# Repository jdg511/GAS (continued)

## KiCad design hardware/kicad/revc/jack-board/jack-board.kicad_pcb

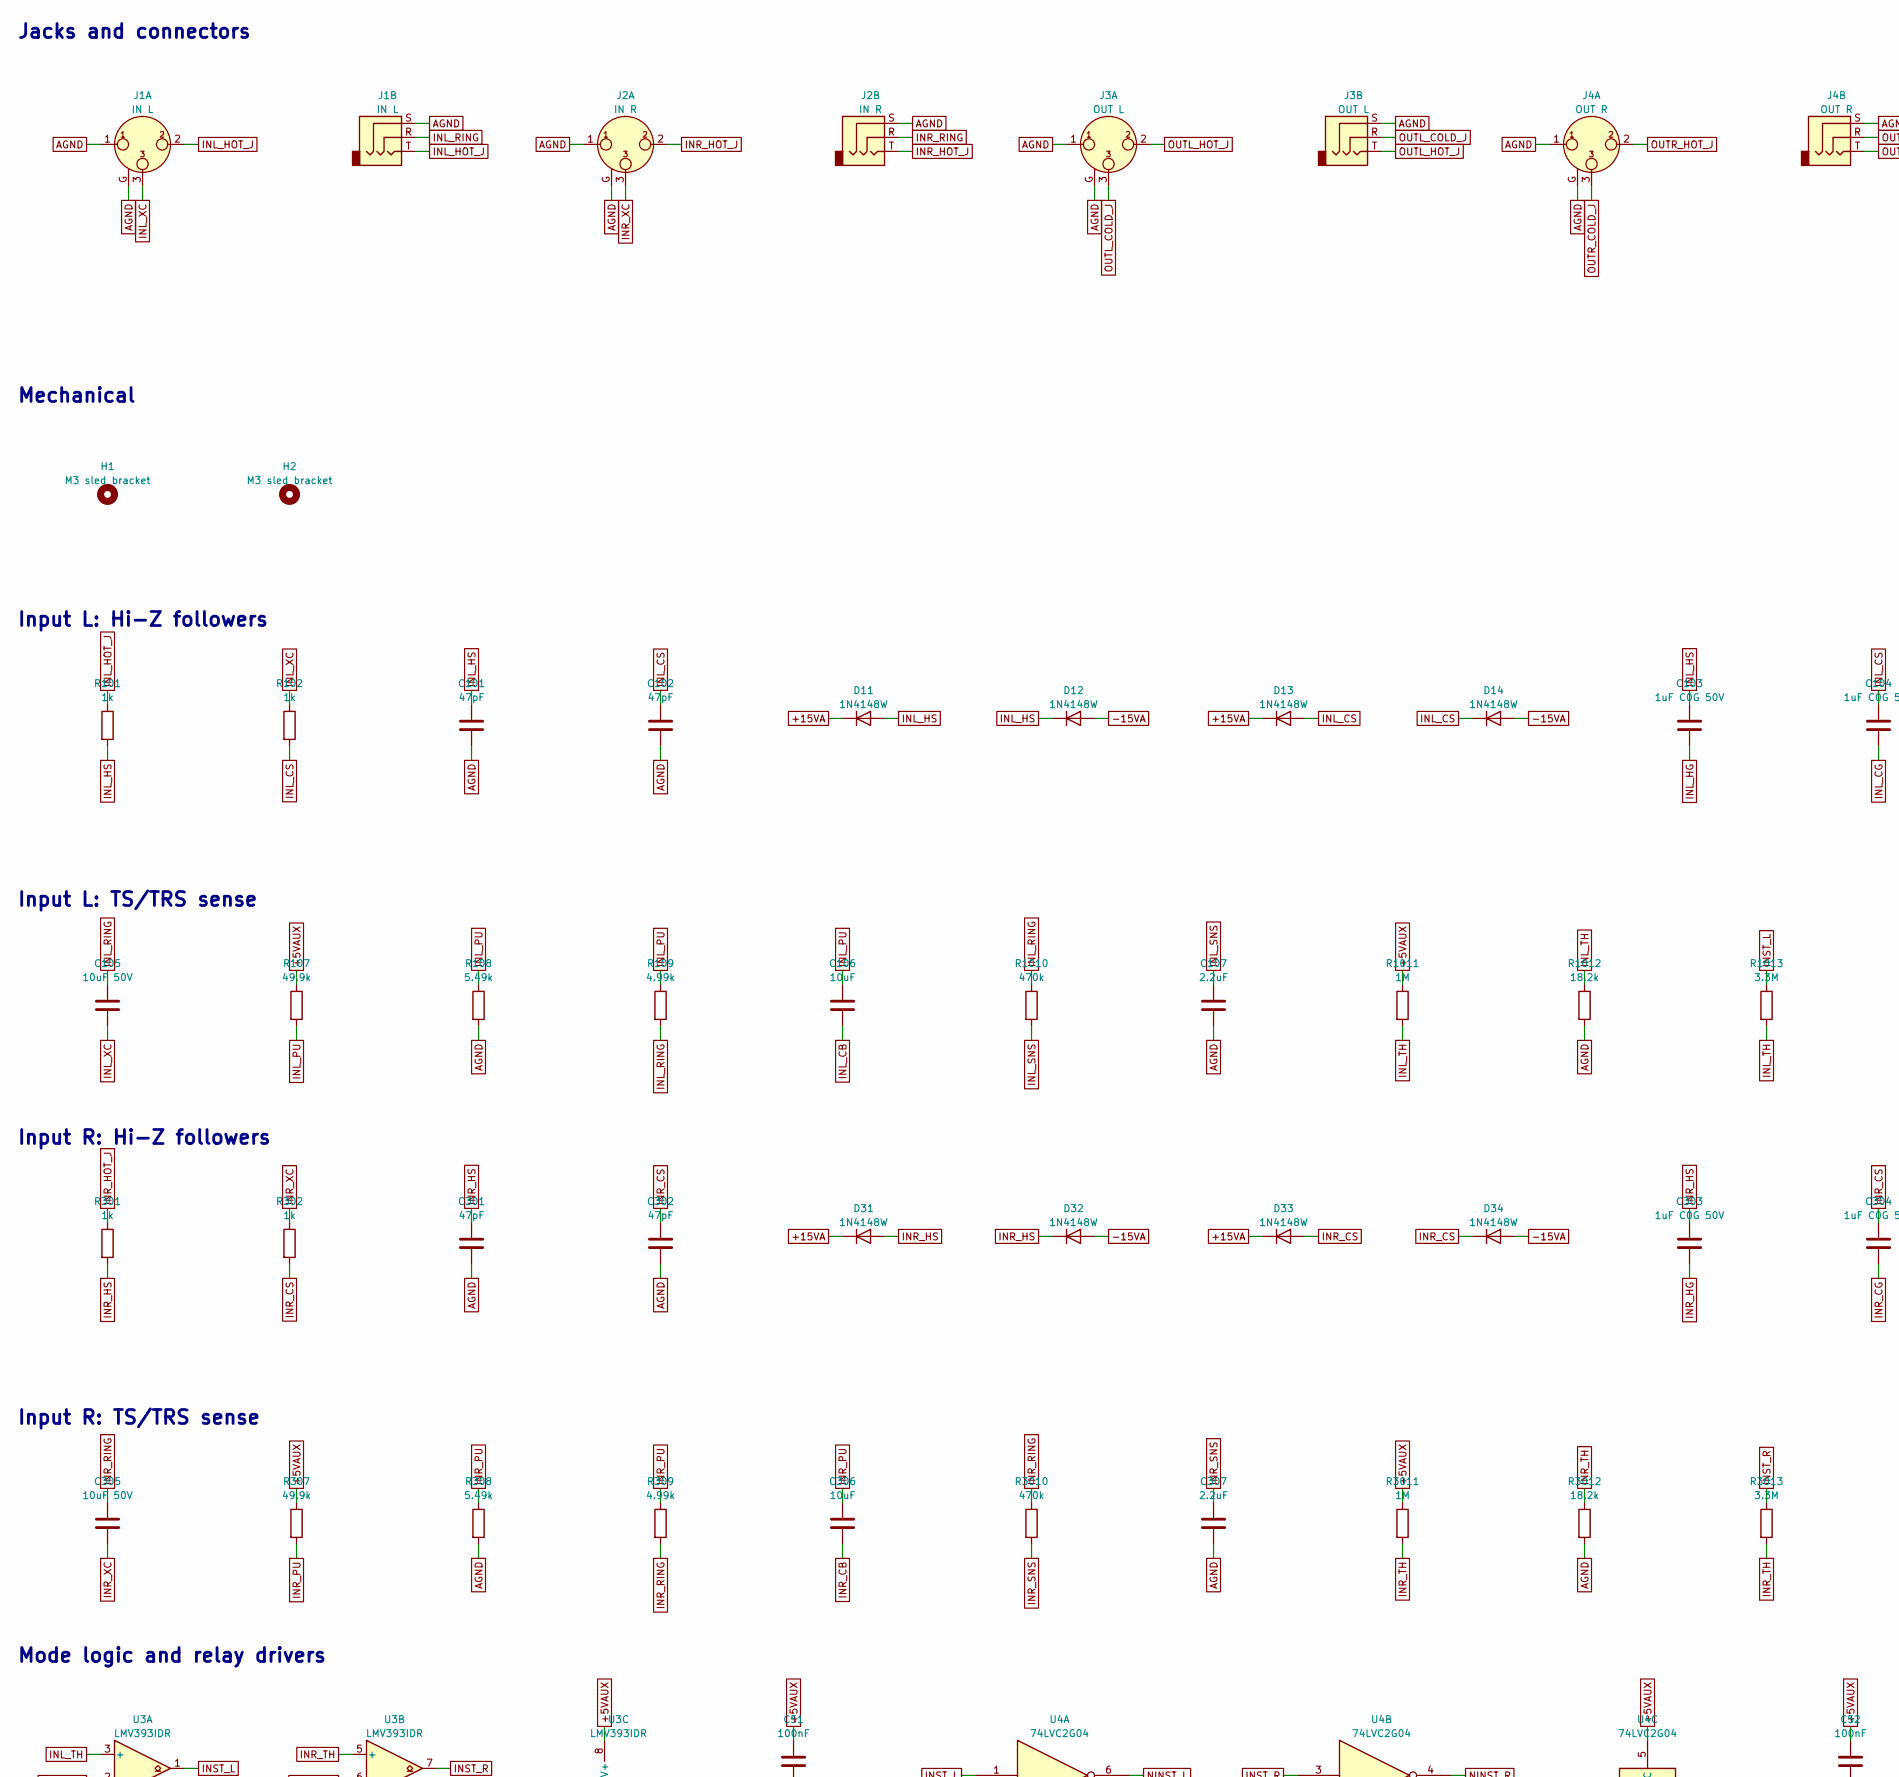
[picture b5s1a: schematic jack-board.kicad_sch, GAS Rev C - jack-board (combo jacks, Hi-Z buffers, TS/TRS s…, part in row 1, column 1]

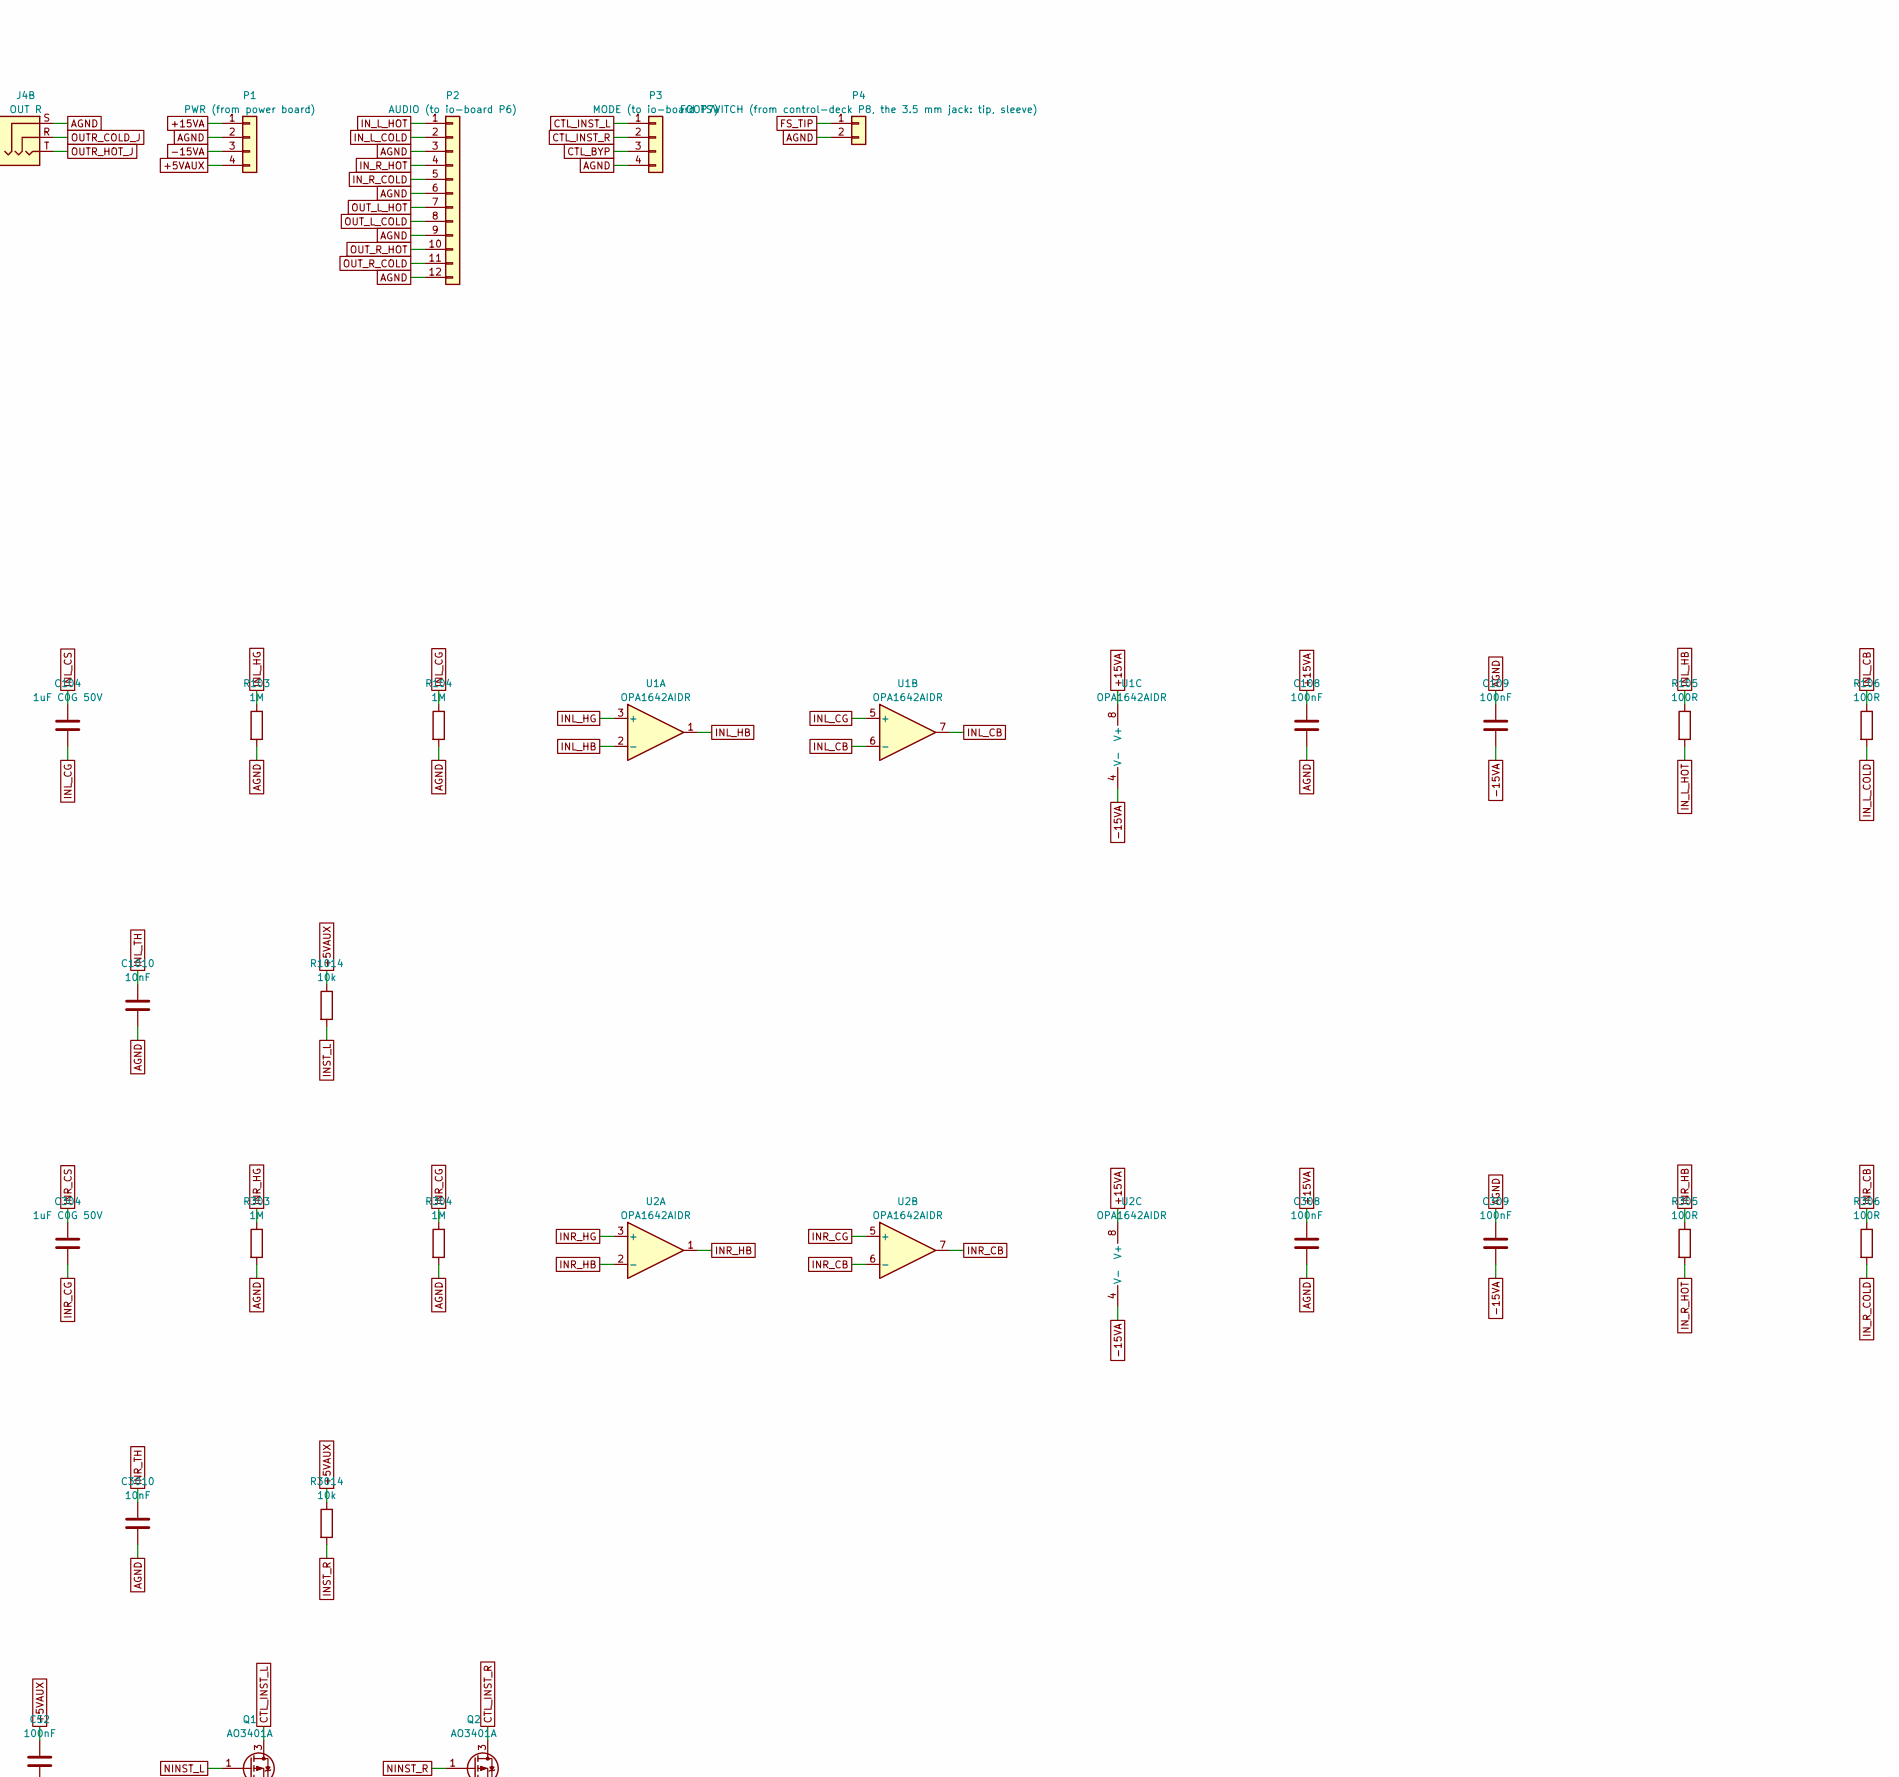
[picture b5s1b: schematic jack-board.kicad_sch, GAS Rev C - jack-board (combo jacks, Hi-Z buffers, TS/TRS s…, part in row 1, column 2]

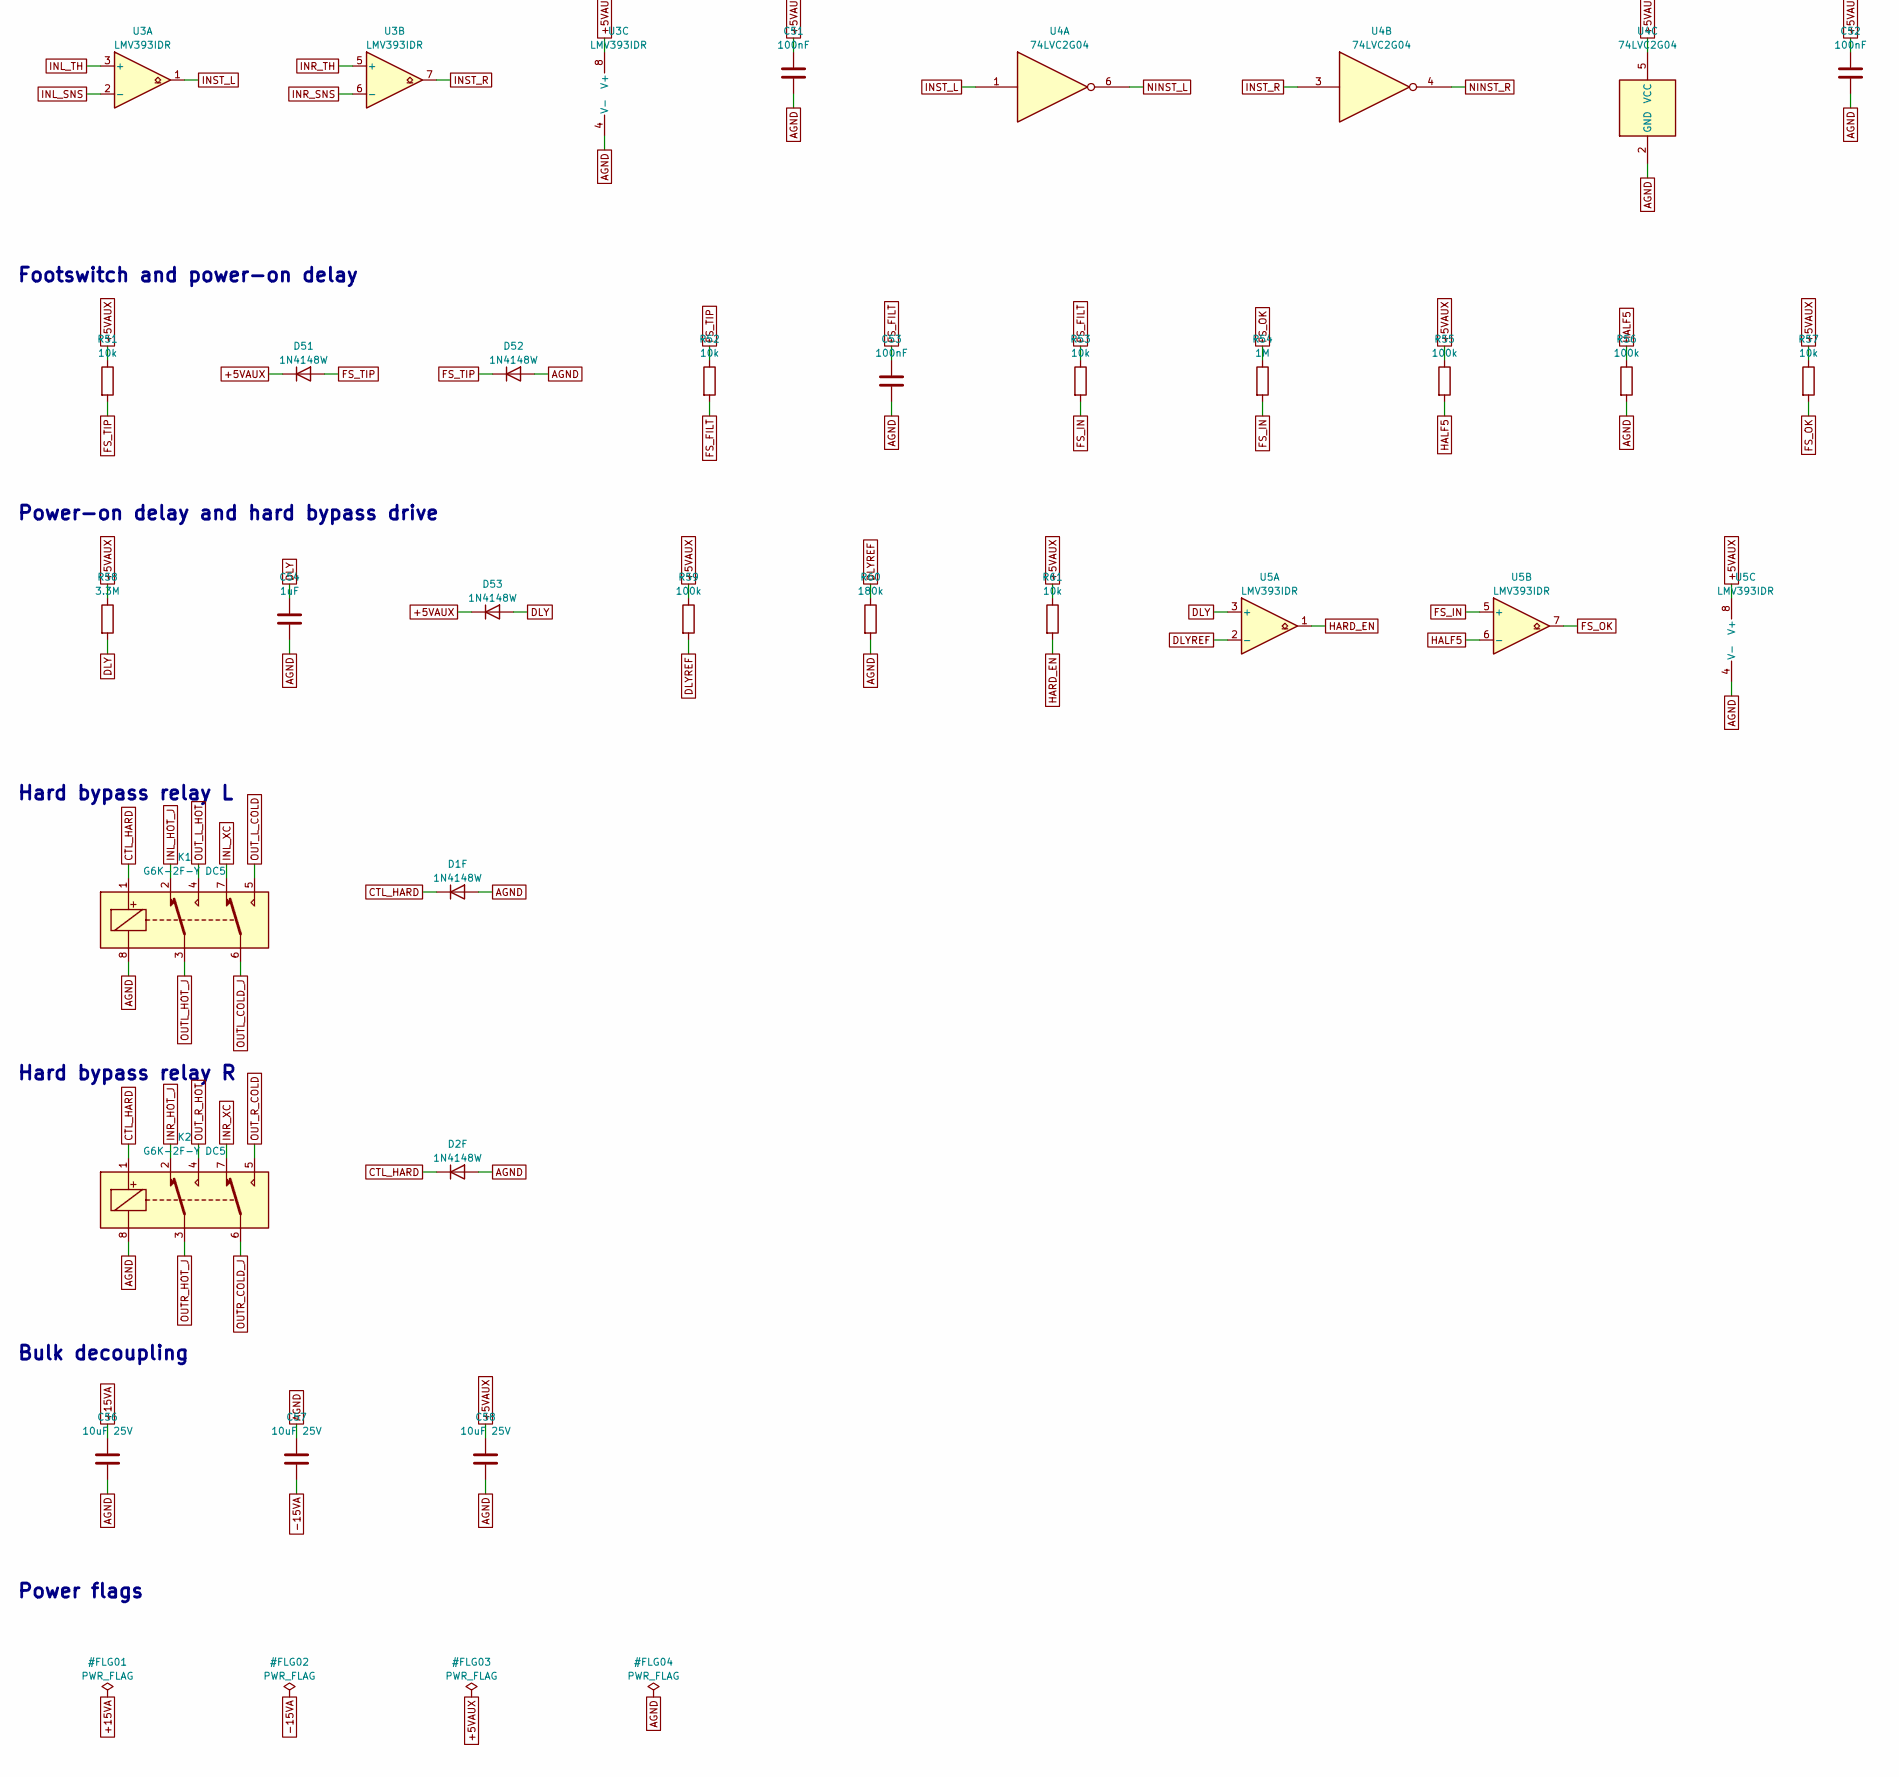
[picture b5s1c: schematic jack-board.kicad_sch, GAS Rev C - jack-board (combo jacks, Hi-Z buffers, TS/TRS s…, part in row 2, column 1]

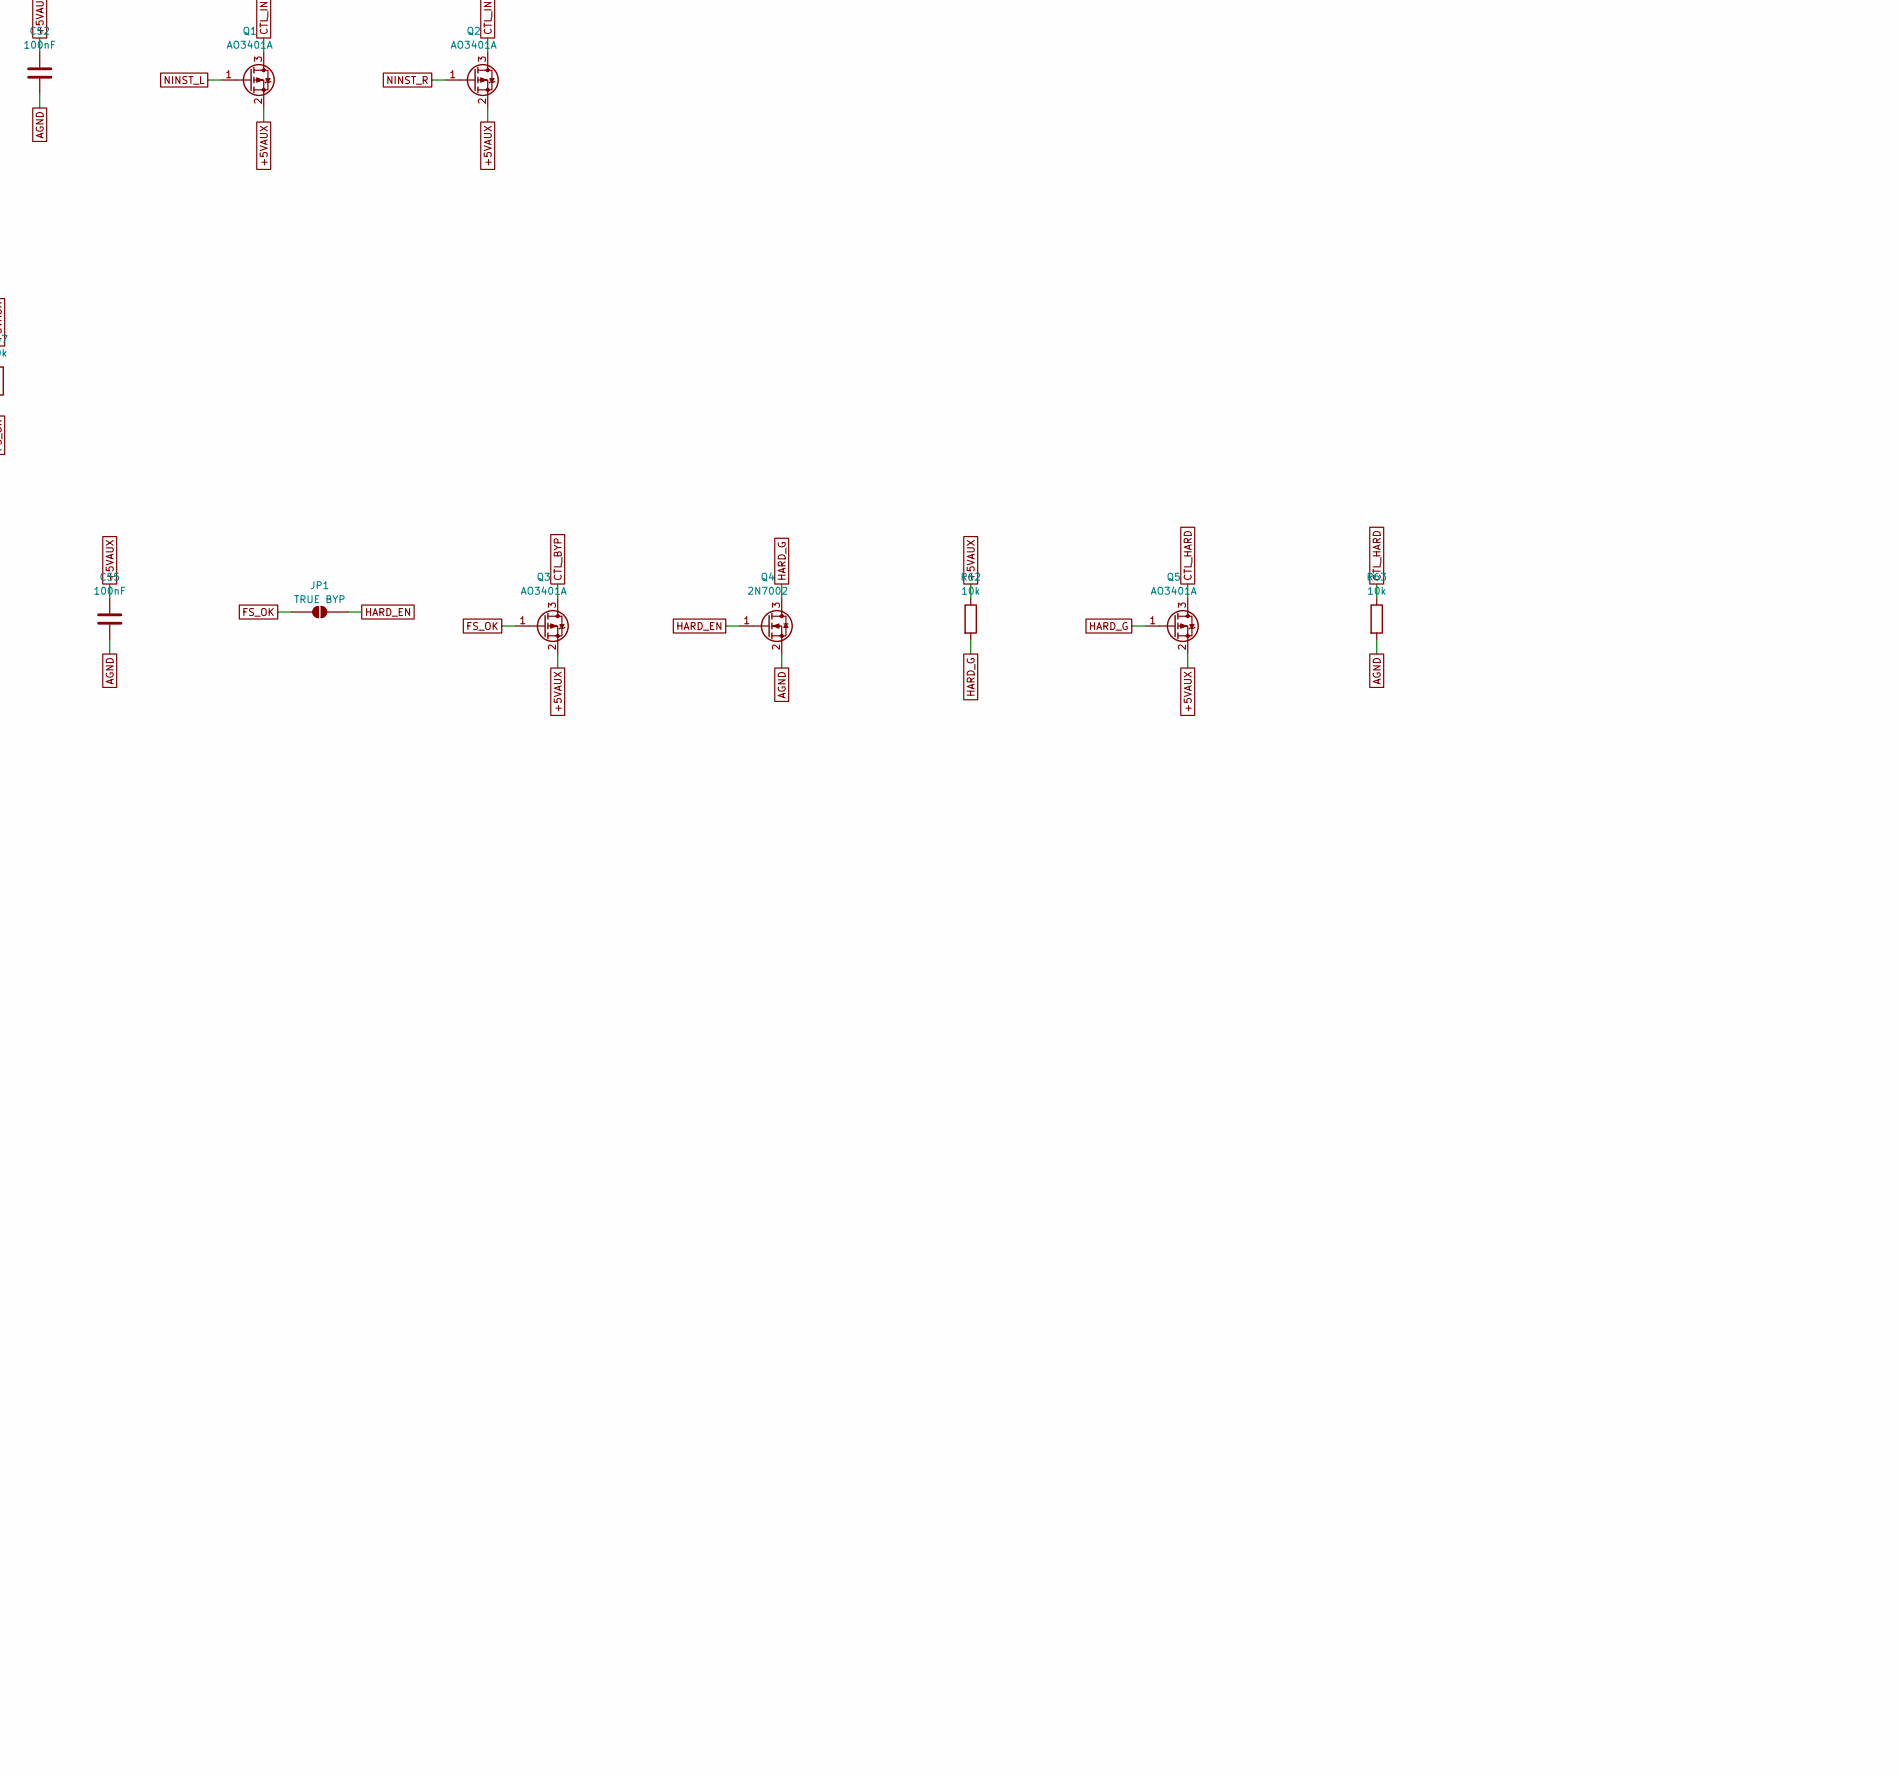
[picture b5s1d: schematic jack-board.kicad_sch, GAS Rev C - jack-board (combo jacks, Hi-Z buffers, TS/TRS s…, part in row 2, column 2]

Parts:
C51, C52, C53, C55, C108, C109, C308, C309: 100nF; C_0603_1608Metric; MPN CL10B104KB8NNNC
C54: 1uF; C_0805_2012Metric; MPN CL21B105KBFNNNE
C56, C57, C58: 10uF 25V; C_0805_2012Metric; MPN CL21A106KAYNNNE
C101, C102, C301, C302: 47pF; C_0603_1608Metric; MPN CL10C470JB8NNNC
C103, C104, C303, C304: 1uF C0G 50V; C_1210_3225Metric; MPN C3225C0G1H105J250AA
C105, C305: 10uF 50V; C_1206_3216Metric; MPN CL31A106KBHNNNE
C106, C306: 10uF; C_0805_2012Metric; MPN CL21A106KAYNNNE
C107, C307: 2.2uF; C_0805_2012Metric; MPN CL21A225KAFNNNE
C1010, C3010: 10nF; C_0603_1608Metric; MPN CL10B103KB8NNNC
D1F, D2F, D11, D12, D13, D14, D31, D32, D33, D34, D51, D52, D53: 1N4148W; D_SOD-123; MPN 1N4148W-7-F
H1, H2: M3 sled bracket; MountingHole_3.2mm_M3
J1: IN L; Jack_XLR-6.35mm_Neutrik_NCJ6FI-V_Vertical; MPN NCJ6FI-V
J2: IN R; Jack_XLR-6.35mm_Neutrik_NCJ6FI-V_Vertical; MPN NCJ6FI-V
J3: OUT L; Jack_XLR-6.35mm_Neutrik_NCJ6FI-V_Vertical; MPN NCJ6FI-V
J4: OUT R; Jack_XLR-6.35mm_Neutrik_NCJ6FI-V_Vertical; MPN NCJ6FI-V
JP1: TRUE BYP; SolderJumper-2_P1.3mm_Open_RoundedPad1.0x1.5mm
K1, K2: G6K-2F-Y DC5; Relay_DPDT_Omron_G6K-2F-Y; MPN G6K-2F-Y DC5
P1: PWR (from power board); JST_VH_B4P-VH_1x04_P3.96mm_Vertical; MPN B4P-VH(LF)(SN)
P2: AUDIO (to io-board P6); JST_XH_B12B-XH-A_1x12_P2.50mm_Vertical; MPN B12B-XH-A(LF)(SN)
P3: MODE (to io-board P7); JST_XH_B4B-XH-A_1x04_P2.50mm_Vertical; MPN B4B-XH-A(LF)(SN)
P4: FOOTSWITCH (from control-deck P8, the 3.5 mm jack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; JST_XH_B2B-XH-A_1x02_P2.50mm_Vertical; MPN B2B-XH-A(LF)(SN)
Q1, Q2, Q3, Q5: AO3401A; SOT-23; MPN AO3401A
Q4: 2N7002; SOT-23; MPN 2N7002-7-F
R51, R52, R53, R57, R61, R62, R63, R1014, R3014: 10k; R_0603_1608Metric; MPN RC0603FR-0710KL
R54, R103, R104, R303, R304, R1011, R3011: 1M; R_0603_1608Metric; MPN RC0603FR-071ML
R55, R56, R59: 100k; R_0603_1608Metric; MPN RC0603FR-07100KL
R58, R1013, R3013: 3.3M; R_0603_1608Metric; MPN RC0603FR-073M3L
R60: 180k; R_0603_1608Metric; MPN RC0603FR-07180KL
R101, R102, R301, R302: 1k; R_0603_1608Metric; MPN RC0603FR-071KL
R105, R106, R305, R306: 100R; R_0603_1608Metric; MPN RC0603FR-07100RL
R107, R307: 49.9k; R_0603_1608Metric; MPN RC0603FR-0749K9L
R108, R308: 5.49k; R_0603_1608Metric; MPN RC0603FR-075K49L
R109, R309: 4.99k; R_0603_1608Metric; MPN RC0603FR-074K99L
R1010, R3010: 470k; R_0603_1608Metric; MPN RC0603FR-07470KL
R1012, R3012: 18.2k; R_0603_1608Metric; MPN RC0603FR-0718K2L
U1, U2: OPA1642AIDR; SOIC-8_3.9x4.9mm_P1.27mm; MPN OPA1642AIDR
U3, U5: LMV393IDR; SOIC-8_3.9x4.9mm_P1.27mm; MPN LMV393IDR
U4: 74LVC2G04; SOT-23-6; MPN 74LVC2G04GV,125

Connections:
+5VAUX: C51.1, C52.1, C55.1, C58.1, D51.1 (K), D53.1 (K), P1.4, Q1.2 (S), Q2.2 (S), Q3.2 (S), Q5.2 (S), R51.1, R55.1, R57.1, R58.1, R59.1, R61.1, R62.1, R107.1, R307.1, R1011.1, R1014.1, R3011.1, R3014.1, U3.8 (V+), U4.5 (VCC), U5.8 (V+)
+15VA: C56.1, C108.1, C308.1, D11.1 (K), D13.1 (K), D31.1 (K), D33.1 (K), P1.1, U1.8 (V+), U2.8 (V+)
-15VA: C57.2, C109.2, C309.2, D12.2 (A), D14.2 (A), D32.2 (A), D34.2 (A), P1.3, U1.4 (V-), U2.4 (V-)
AGND: C51.2, C52.2, C53.2, C54.2, C55.2, C56.2, C57.1, C58.2, C101.2, C102.2, C107.2, C108.2, C109.1, C301.2, C302.2, C307.2, C308.2, C309.1, C1010.2, C3010.2, D1F.2 (A), D2F.2 (A), D52.2 (A), J1.1, J1.G, J1.S, J2.1, J2.G, J2.S, J3.1, J3.G, J3.S, J4.1, J4.G, J4.S, K1.8, K2.8, P1.2, P2.3, P2.6, P2.9, P2.12, P3.4, P4.2, Q4.2 (S), R56.2, R60.2, R63.2, R103.2, R104.2, R108.2, R303.2, R304.2, R308.2, R1012.2, R3012.2, U3.4 (V-), U4.2 (GND), U5.4 (V-)
CTL_BYP: P3.3, Q3.3 (D)
CTL_HARD: D1F.1 (K), D2F.1 (K), K1.1, K2.1, Q5.3 (D), R63.1
CTL_INST_L: P3.1, Q1.3 (D)
CTL_INST_R: P3.2, Q2.3 (D)
DLY: C54.1, D53.2 (A), R58.2, U5.3 (+)
DLYREF: R59.2, R60.1, U5.2 (-)
FS_FILT: C53.1, R52.2, R53.1
FS_IN: R53.2, R54.2, U5.5 (+)
FS_OK: JP1.1 (A), Q3.1 (G), R54.1, R57.2, U5.7
FS_TIP: D51.2 (A), D52.1 (K), P4.1, R51.2, R52.1
HALF5: R55.2, R56.1, U5.6 (-)
HARD_EN: JP1.2 (B), Q4.1 (G), R61.2, U5.1
HARD_G: Q4.3 (D), Q5.1 (G), R62.2
INL_CB: C106.2, R106.1, U1.6 (-), U1.7
INL_CG: C104.2, R104.1, U1.5 (+)
INL_CS: C102.1, C104.1, D13.2 (A), D14.1 (K), R102.2
INL_HB: R105.1, U1.1, U1.2 (-)
INL_HG: C103.2, R103.1, U1.3 (+)
INL_HOT_J: J1.2, J1.T, K1.2, R101.1
INL_HS: C101.1, C103.1, D11.2 (A), D12.1 (K), R101.2
INL_PU: C106.1, R107.2, R108.1, R109.1
INL_RING: C105.1, J1.R, R109.2, R1010.1
INL_SNS: C107.1, R1010.2, U3.2 (-)
INL_TH: C1010.1, R1011.2, R1012.1, R1013.2, U3.3 (+)
INL_XC: C105.2, J1.3, K1.7, R102.1
INR_CB: C306.2, R306.1, U2.6 (-), U2.7
INR_CG: C304.2, R304.1, U2.5 (+)
INR_CS: C302.1, C304.1, D33.2 (A), D34.1 (K), R302.2
INR_HB: R305.1, U2.1, U2.2 (-)
INR_HG: C303.2, R303.1, U2.3 (+)
INR_HOT_J: J2.2, J2.T, K2.2, R301.1
INR_HS: C301.1, C303.1, D31.2 (A), D32.1 (K), R301.2
INR_PU: C306.1, R307.2, R308.1, R309.1
INR_RING: C305.1, J2.R, R309.2, R3010.1
INR_SNS: C307.1, R3010.2, U3.6 (-)
INR_TH: C3010.1, R3011.2, R3012.1, R3013.2, U3.5 (+)
INR_XC: C305.2, J2.3, K2.7, R302.1
INST_L: R1013.1, R1014.2, U3.1, U4.1
INST_R: R3013.1, R3014.2, U3.7, U4.3
IN_L_COLD: P2.2, R106.2
IN_L_HOT: P2.1, R105.2
IN_R_COLD: P2.5, R306.2
IN_R_HOT: P2.4, R305.2
NINST_L: Q1.1 (G), U4.6
NINST_R: Q2.1 (G), U4.4
OUTL_COLD_J: J3.3, J3.R, K1.6
OUTL_HOT_J: J3.2, J3.T, K1.3
OUTR_COLD_J: J4.3, J4.R, K2.6
OUTR_HOT_J: J4.2, J4.T, K2.3
OUT_L_COLD: K1.5, P2.8
OUT_L_HOT: K1.4, P2.7
OUT_R_COLD: K2.5, P2.11
OUT_R_HOT: K2.4, P2.10

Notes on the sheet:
Jacks and connectors
Mechanical
Input L: Hi-Z followers
Input L: TS/TRS sense
Input R: Hi-Z followers
Input R: TS/TRS sense
Mode logic and relay drivers
Footswitch and power-on delay
Power-on delay and hard bypass drive
Hard bypass relay L
Hard bypass relay R
Bulk decoupling
Power flags

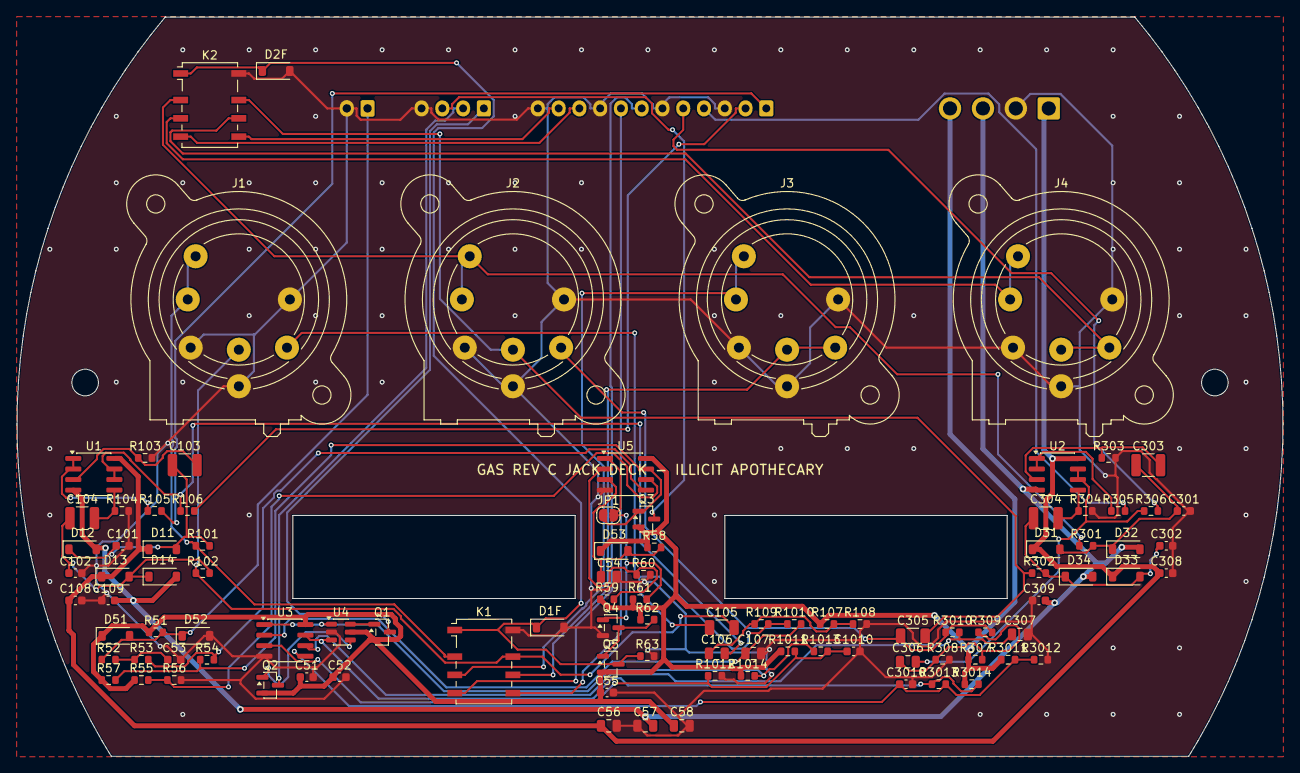
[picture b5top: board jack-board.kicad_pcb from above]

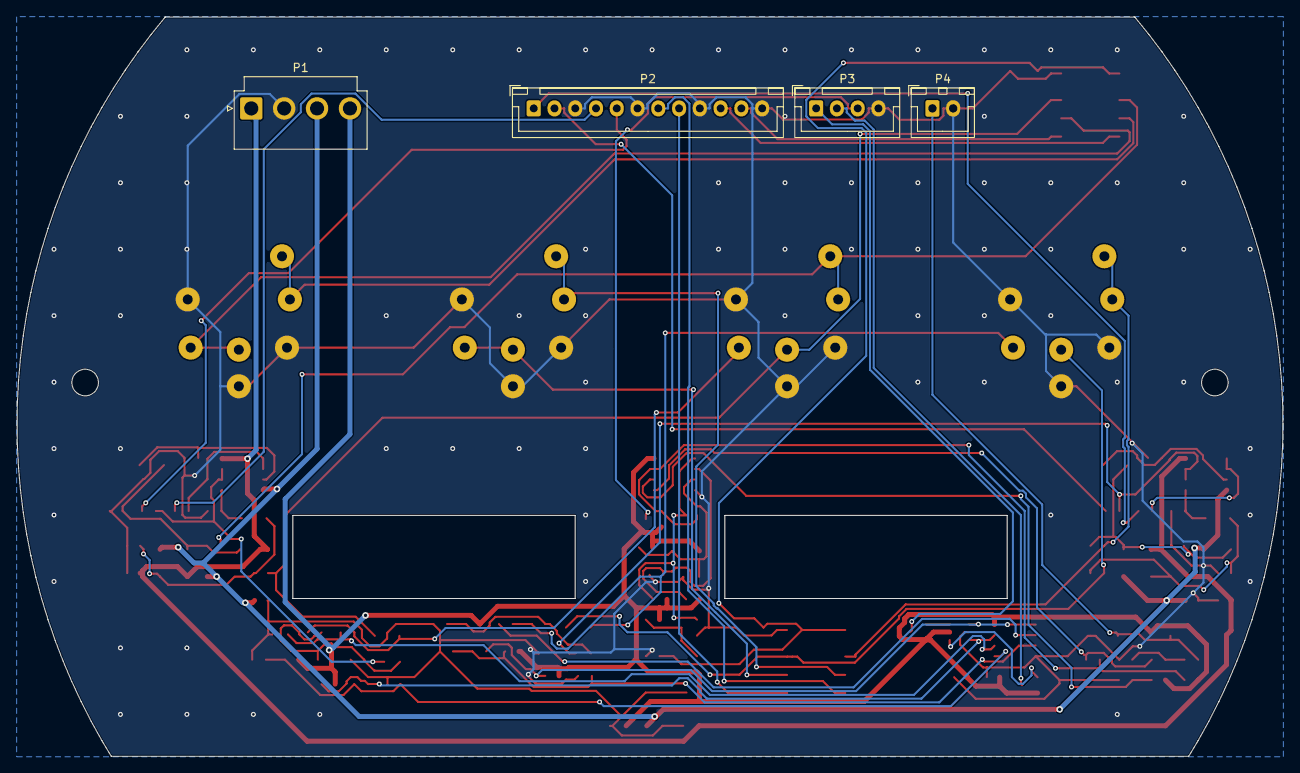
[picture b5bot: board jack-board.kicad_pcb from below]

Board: 2 copper layers, 152.4 x 89.0 mm, 105 parts (4 on the bottom side), 57 nets.
